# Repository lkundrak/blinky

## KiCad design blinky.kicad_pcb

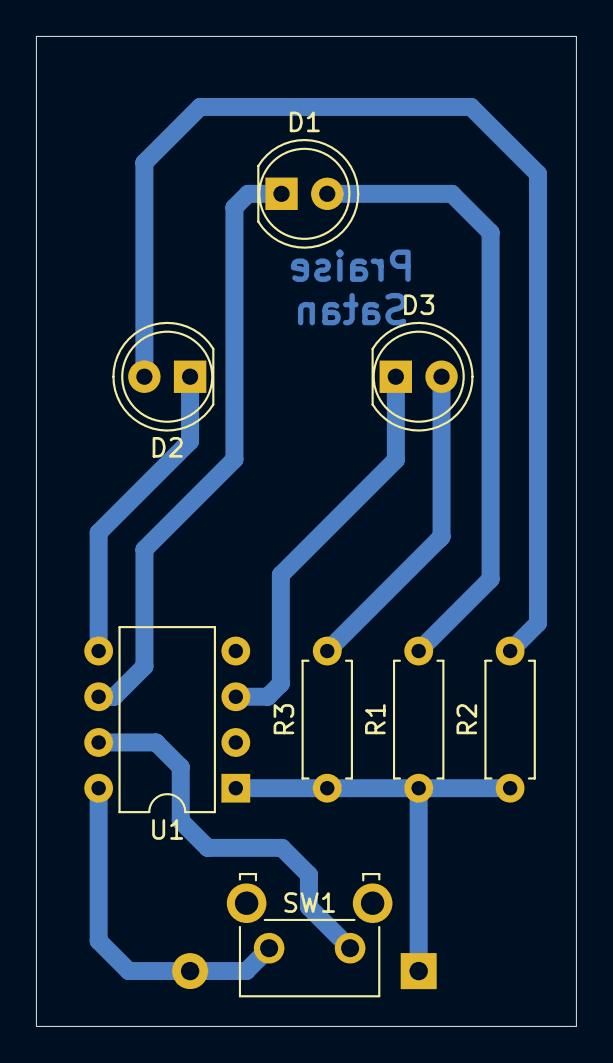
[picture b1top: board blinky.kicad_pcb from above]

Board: 2 copper layers, 30.0 x 55.0 mm, 9 parts (1 on the bottom side), 9 nets.

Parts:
BT1: Battery; BatteryHolder_Keystone_2468_2xAAA
D1, D2, D3: LED_Small; LED_D5.0mm
R1, R2, R3: 150R; R_Axial_DIN0207_L6.3mm_D2.5mm_P7.62mm_Horizontal
SW1: SW_Push; SW_Tactile_SKHH_Angled
U1: PIC12F1822-IP; DIP-8_W7.62mm

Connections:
GND: BT1.2, SW1.2, U1.8
unnamed: D1.1, U1.6
unnamed: D1.2, R1.2
unnamed: D2.1, U1.5
unnamed: D2.2, R2.2
unnamed: D3.1, U1.3
unnamed: D3.2, R3.2
unnamed: SW1.1, U1.7
VCC: BT1.1, R1.1, R2.1, R3.1, U1.1

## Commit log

2020-10-21 Initial import
